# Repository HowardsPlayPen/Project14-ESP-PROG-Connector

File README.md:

# Project14-ESP-PROG-Connector

Helper board to allow connecting to ESP32 boards easier - i.e. from PlatformIO I can connect via the USB-C to access this helper boards FTDI chip to then connect onwards to whatever ESP32 I am developing at the time

It allows a Tag Connect cable (TDC2050) to connect to the ESP32 board 

As the connector is 10 pins I could include the power + TX/RX + Boot/Reset also the pins needed for hardware debugging on the same connector. I googled to see if I could find standardised pins for this sort of thing but didnt have any luck, so just made my own.

OR

The board allows the same TDC2050 to be used - but along with an ESP32 debugging board

(Only issue I have with the ESP32-Prog board is that it uses a micro-usb connector rather than a USB-C so I would expect that to really limit what power it can supply to my ESP32 board.)

## Simple screenshot of the PCB

## Simple Kicad 3D representation of the board

## Schematic of TDC 2050 connector on my ESP32 board

This is the schematic of the connector to put on the destination ESP32 board 

Example of connecting this to an ESP32-CAM for both USB monitoring and hardware debugging

## View of the project

I am used to having RX + TX pins on my ESP32 boards or a USB-C connector - but with this project I can just add in the TDC-2050 pinout and then when I want to debug the board it is a simple connection to my PC. I can even hardware debug using the same connector.

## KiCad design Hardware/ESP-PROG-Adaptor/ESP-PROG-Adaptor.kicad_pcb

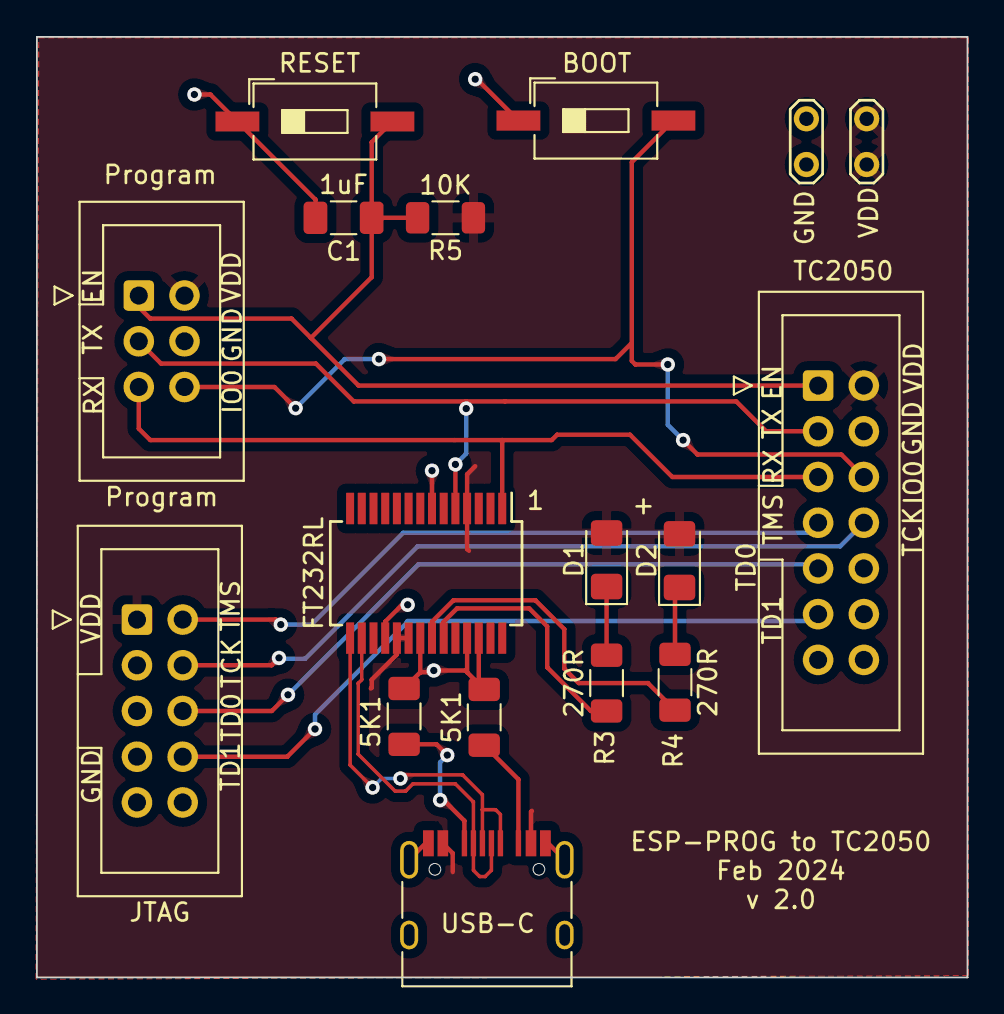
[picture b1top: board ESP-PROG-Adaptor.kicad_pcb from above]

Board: 2 copper layers, 51.7 x 52.2 mm, 17 parts (0 on the bottom side), 18 nets.

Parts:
B1: RESET; SW_DIP_SPSTx01_Slide_6.7x4.1mm_W8.61mm_P2.54mm_LowProfile
B2: BOOT; SW_DIP_SPSTx01_Slide_6.7x4.1mm_W8.61mm_P2.54mm_LowProfile
C1: 1uF; C_1206_3216Metric_Pad1.33x1.80mm_HandSolder
D1, D2: LED; LED_1206_3216Metric_Pad1.42x1.75mm_HandSolder
GND1: GND; TestPoint_2Pads_Pitch2.54mm_Drill0.8mm
J1: JTAG; IDC-Header_2x05_P2.54mm_Vertical
J2: Program; IDC-Header_2x03_P2.54mm_Vertical
J3: TDC2050_Connector; IDC-Header_2x07_P2.54mm_Vertical
J4: USB_C_Receptacle_USB2.0; USB_C_Receptacle_HRO_TYPE-C-31-M-12
R1, R2: 5K1; R_1206_3216Metric_Pad1.30x1.75mm_HandSolder
R3, R4: 270R; R_1206_3216Metric_Pad1.30x1.75mm_HandSolder
R5: 10K; R_1206_3216Metric_Pad1.30x1.75mm_HandSolder
U1: FT232RL; SSOP-28_5.3x10.2mm_P0.65mm
VCC1: VCC; TestPoint_2Pads_Pitch2.54mm_Drill0.8mm

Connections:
D+: J4.A6 (D+), J4.B6 (D+), U1.15 (USBD+)
D-: J4.A7 (D-), J4.B7 (D-), U1.16 (USBD-)
EN: B1.2, C1.1, J2.1, J3.1, R5.2
ESP_TCK: J1.4, J3.8
ESP_TD0: J1.6, J3.9
ESP_TD1: J1.8, J3.11
ESP_TMS: J1.2, J3.7
GND: B1.1, B2.1, C1.2, GND1.1, GND1.2, J1.3, J1.5, J1.7, J1.9, J2.4, J3.4, J4.A1 (GND), J4.A12 (GND), J4.B1 (GND), J4.B12 (GND), J4.S1 (SHIELD), R1.1, R2.1, U1.7 (GND), U1.18 (GND), U1.21 (GND), U1.25 (AGND), U1.26 (TEST)
IO0: B2.2, J2.6, J3.6
unnamed: D1.1 (K), R3.1
unnamed: D2.1 (K), R4.2
unnamed: J4.A5 (CC1), R1.2
unnamed: J4.B5 (CC2), R2.2
unnamed: R3.2, U1.23 (CBUS0)
unnamed: R4.1, U1.22 (CBUS1)
RX: J2.5, J3.5, U1.1 (TXD)
TX: J2.3, J3.3, U1.5 (RXD)
VDD: D1.2 (A), D2.2 (A), J1.1, J2.2, J3.2, J4.A4 (VBUS), J4.A9 (VBUS), J4.B4 (VBUS), J4.B9 (VBUS), R5.1, U1.4 (VCCIO), U1.19 (~RESET), U1.20 (VCC), VCC1.1, VCC1.2
